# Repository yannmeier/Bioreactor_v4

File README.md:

# Bioreactor_v4

This repository is dedicated to the version 4 of the Bioreactor.

## Electronics

The architecture for v4 is articulated around one central board powered by 
an ATmega32u4 MCU relying on nilRTOS and external boards for interfacing
to extra sensors and/or LCD screeens.

The main board comes with the following features:
- stepper motor control with Neodimium magnet
- Load cell based on HX711
- PID heater control
- DS18B20+ temperature sensing
- LoRaWAN mid-range wireless communication
- 2 peristaltic pumps control
- SPI port to control a slave LCD board
- 2 I2C ports for master to slave communication to external modules
- Serial over USB
- 12V DC jack supply

There are already a few external extra modules:
- LCD SPI slave board on ATmega32u4
- pH & Conductommetry regulation I2C slave, also works as a stand alone (in development phase)
- gas flux and mix control with analogic valves, also works as a stand alone (in development phase)
- spectrophotometer immersed in the bioreactor, also works as a stand alone (in development phase)

References:
-https://www.arduino.cc/en/Main/ArduinoBoardLeonardo
-https://github.com/greiman/NilRTOS-Arduino

Revision notes:
Bioreactor V4.2:
- Changed operating frequency from 16MHz to 8MHz
- Changed operating voltage from 5V to 3.3V
- Removed 5V regulation
- Routed LoRa RST pin to MCU with additionnal pull-up
- Hack to be performed on hardware (D6<>D12) for software compatibility
Bioreactor V4.3:
- Stepper motor has individually controllable phases
- LoRa SMA PCB edge Antenna support
- Hack to be performed on hardware (D6<>D12) for software compatibility
Bioreactor V4.4:
- D6<>D12 exchanged to provide PWM PID control of the heater

## Mechanics

(Documentation coming soon)

#Bioreactor_v5

In parallel to the development of the version 4 of the Bioreactor, a version 5, relying on the 
more powerful SAMD21 (Cortex M0+ ARM) MCU and FreeRTOS is currently being studied.

References:
-https://www.arduino.cc/en/Main/ArduinoBoardZero
-http://www.freertos.org/Atmel_SAMD20_RTOS.html
-https://www.kickstarter.com/projects/rabidprototypes/neutrino-the-tiny-32-bit-arduino-zero-compatible/updates

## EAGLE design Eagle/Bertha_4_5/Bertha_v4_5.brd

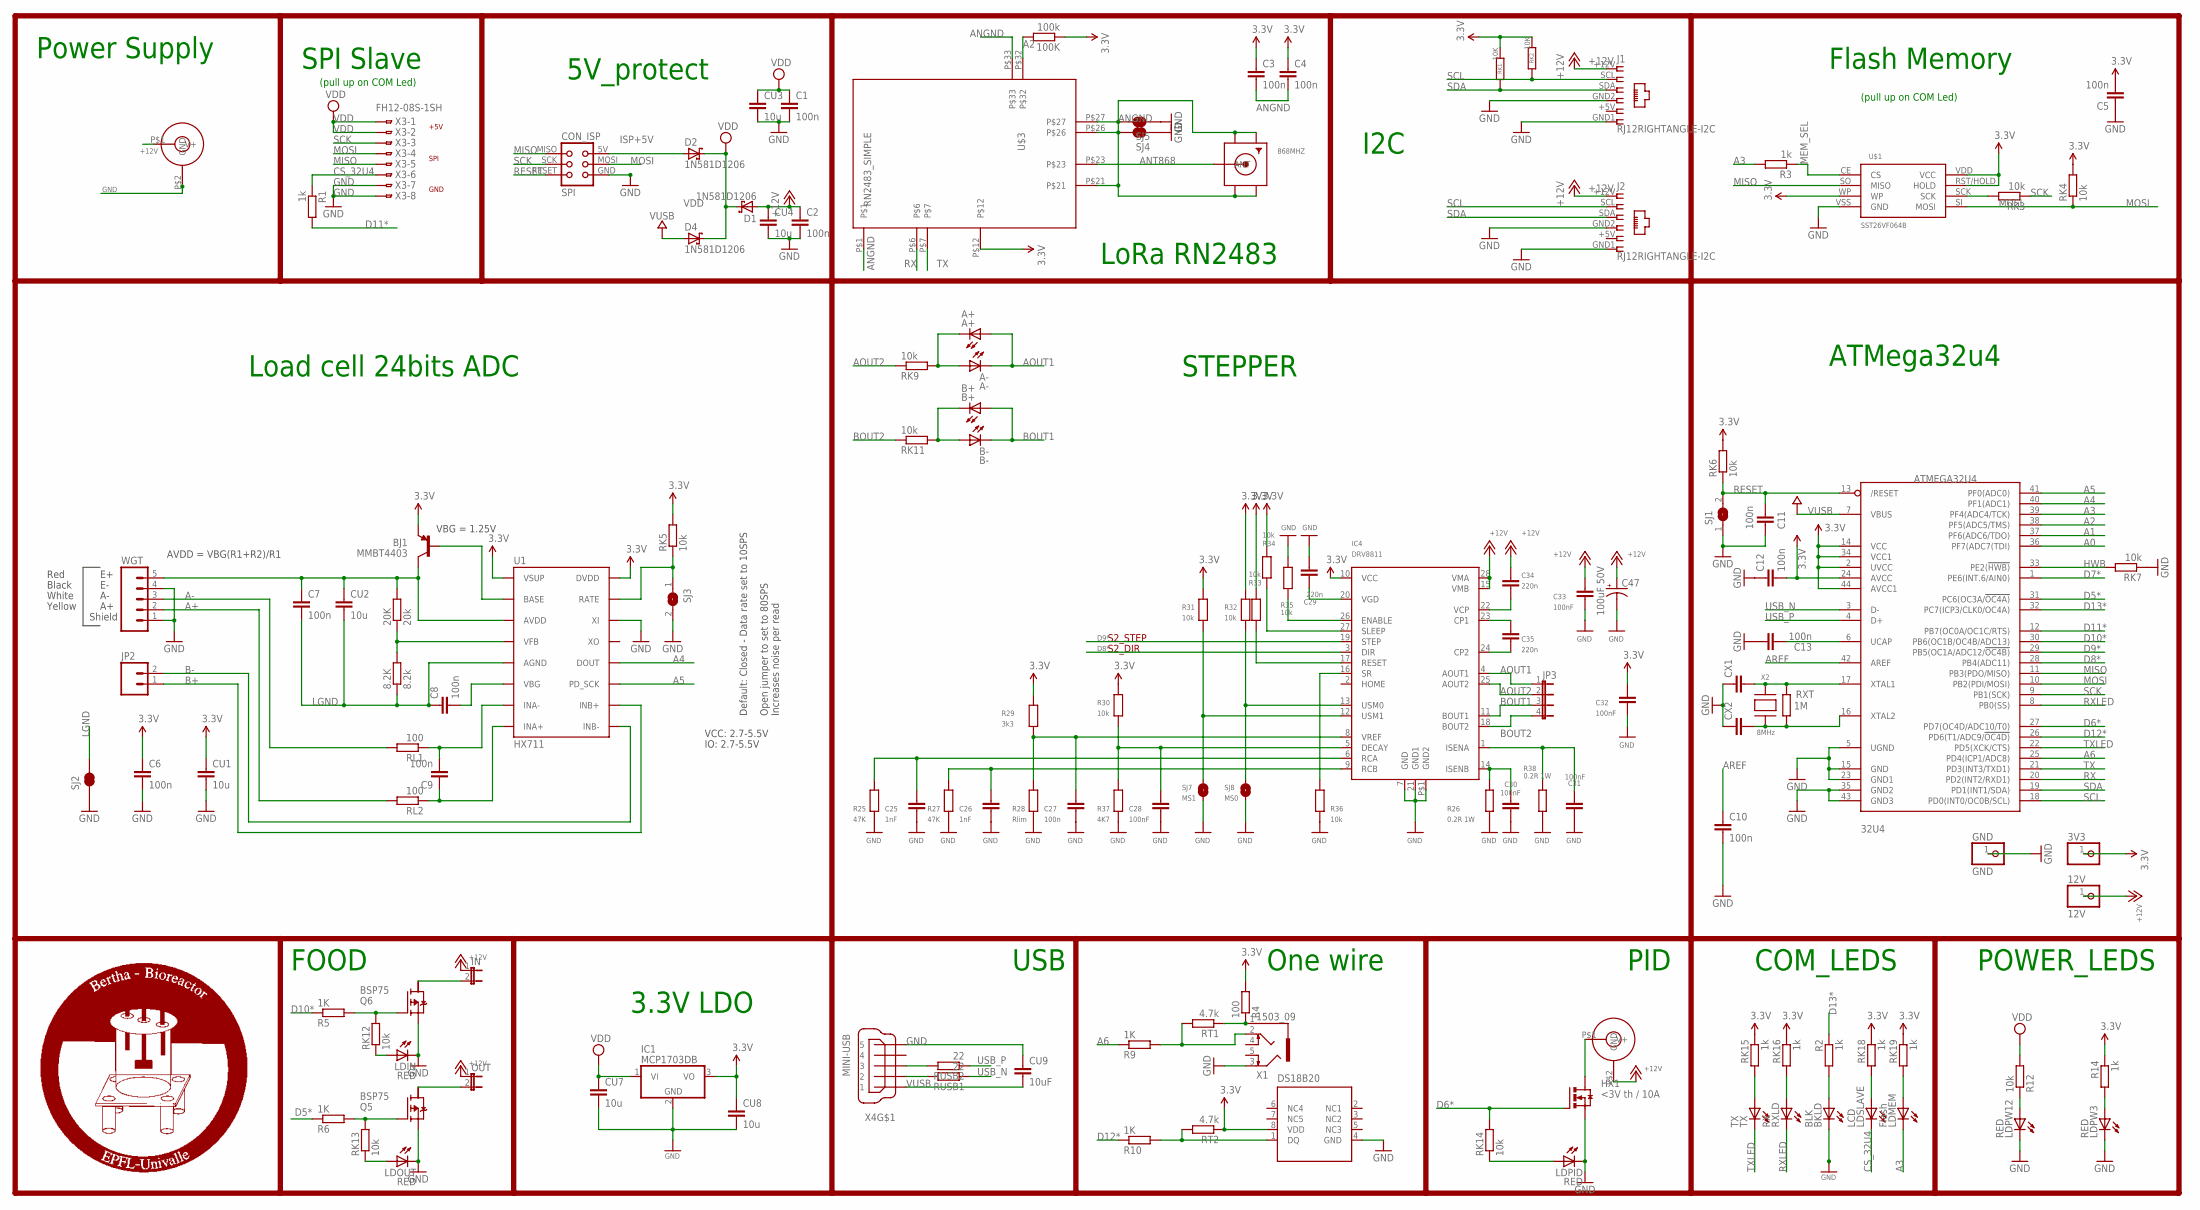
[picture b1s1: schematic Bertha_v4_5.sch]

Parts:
3V3: PINHD-1X1; 1X01
8.2K: 8.2k; M0805
12V: 12V; 1X01
20K: 20k; M0805
32U4: ATMEGA32U4; TQFP44
100K: 100k; R0805
868MHZ: SMACONNECTOR_EDGE; SMA_EDGELAUNCH
A+: A+; CHIP-LED0805
A-: A-; CHIP-LED0805
B+: B+; CHIP-LED0805
B-: B-; CHIP-LED0805
BJ1: MMBT4403; SOT23-3
BKLD: BLK; CHIP-LED0805
C1, C2, C3, C4, C5, C6, C7, C8, C9, C10, C11, C12, C13: 100n; C0805
C25, C26: 1nF; 0805
C27: 100n; 0805
C28, C30, C31, C32, C33: 100nF; 0805
C29, C34, C35: 220n; 0805
C47: 100uF 50V; PANASONIC_E
CON1, CON2: JACK_DC_BARREL; DC_BARREL
CON_ISP: SPI; TC2030-MCP-NL
CU1, CU2, CU3, CU4, CU7, CU8: 10u; C0805
CU9: 10uF; C0805
CX1, CX2: 22pF; C0805
D1, D2, D4: 1N581D1206; LED-1206
GND: GND; 1X01
HX1: <3V th / 10A; D2PACK
IC1: MCP1703DB; SOT223
IC4: DRV8811; HTSSOP28
IN: JP1E; JP1
J1, J2: RJ12RIGHTANGLE-I2C; RJ12-RIGHTANGLE-I2C
JP2: M02PTH; 1X02
JP3: JP4E; JP4
LDIN: RED; CHIP-LED0805
LDMEM: Flash; CHIP-LED0805
LDOUT: RED; CHIP-LED0805
LDPID: RED; CHIP-LED0805
LDPW3, LDPW12: RED; CHIP-LED0805
LDSLAVE: LCD; CHIP-LED0805
OUT: JP1E; JP1
Q5, Q6: BSP75; PG-SOT-223
R1, R2, R3, R14: 1k; R0805
R4: 100; R0805
R5, R6, R9, R10: 1K; R0805
R12: 10k; R0805
R25, R27: 47K; 0805
R26, R38: 0.2R 1W; R2010
R28: Rlim; 0805
R29: 3k3; 0805
R30, R31, R32, R33, R34, R35, R36: 10k; 0805
R37: 4K7; 0805
RK1, RK2: 10K; M0805
RK3, RK4, RK9, RK11, RK12, RK13, RK14: 10k; R0805
RK5, RK6, RK7: 10k; M0805
RK15, RK16, RK18, RK19: 1k; R0805
RL1, RL2: 100; M0805
RT1, RT2: 4.7k; R0805
RUSB1, RUSB2: 22; M0805
RXLD: RX; CHIP-LED0805
RXT: 1M; R0805
SJ1, SJ3: SJ
SJ2, SJ4, SJ5: JUMPER-PAD-2-NC_BY_TRACE; PAD-JUMPER-2-NC_BY_TRACE_YES_SILK
SJ7: MS1; SJ
SJ8: MS0; SJ
TX: TX; CHIP-LED0805
U1: HX711; SO16
U$1: SST26VF064B; SOIC_8-LEAD
U$2: DS18B20; MSOP8
U$3: RN2483_SIMPLE
WGT: M05PTH; 1X05
X1: 1503_09
X2: 8MHz; NX6035
X3: FH12-08S-1SH
X4: MINI-USB; 32005-201

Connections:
3.3V: 3V3.1, 32U4.2 (UVCC), 32U4.14 (VCC), 32U4.24 (AVCC), 32U4.34 (VCC1), 32U4.44 (AVCC1), 100K.1, BJ1.2 (E), C3.1, C4.1, C5.2, C6.1, C12.2, C32.1, CU1.1, CU8.1, IC1.3 (VO), IC4.10 (VCC), R4.2, R14.1, R29.2, R30.2, R31.2, R32.2, R33.2, R34.2, RK1.1, RK2.1, RK4.2, RK5.2, RK6.2, RK15.1, RK16.1, RK18.1, RK19.1, RT2.1, U1.1 (VSUP), U1.16 (DVDD), U$1.RST/HOLD (HOLD), U$1.VDD (VCC), U$1.WP, U$2.8 (VDD), U$3.P$12
5: J1.+5V (5), J2.+5V (5)
+12V: 12V.1, C2.1, C33.1, C34.1, C47.+, CON1.P$1 (V+), CON2.P$2 (GND), CU4.1, D1.A, IC4.15 (VMB), IC4.28 (VMA), IN.1, J1.+12V (1), J2.+12V (1), OUT.1
A0: 32U4.36 (PF7(ADC7(TDI))
A1: 32U4.37 (PF6(ADC6/TDO))
A2: 32U4.38 (PF5(ADC5/TMS)), 100K.2, U$3.P$32
A3: 32U4.39 (PF4(ADC4/TCK)), LDMEM.C, R3.2
A4: 32U4.40 (PF1(ADC1)), U1.12 (DOUT)
A5: 32U4.41 (PF0(ADC0)), U1.11 (PD_SCK)
A6: 32U4.25 (PD4(ICP1/ADC8)), R9.1
A+: RL2.2, WGT.2
A-: RL1.2, WGT.3
ANGND: 868MHZ.GND@1 (GND4), 868MHZ.GND@2 (GND3), 868MHZ.GND@3 (GND2), 868MHZ.GND@4 (GND1), C3.2, C4.2, SJ4.2, SJ5.2, U$3.P$1, U$3.P$21, U$3.P$26, U$3.P$27, U$3.P$33
ANT868: 868MHZ.P (ANT), U$3.P$23
AOUT1: A+.A, A-.C, IC4.4 (AOUT1), JP3.1
AOUT2: IC4.25 (AOUT2), JP3.2, RK9.1
AREF: 32U4.42 (AREF), C10.1
B+: JP2.1, U1.10 (INB+)
B-: JP2.2, U1.9 (INB-)
BOUT1: B+.A, B-.C, IC4.11 (BOUT1), JP3.3
BOUT2: IC4.18 (BOUT2), JP3.4, RK11.1
CN3: C8.2, U1.6 (VBG)
CS_32U4: LDSLAVE.C, R1.1, X3.6
D5*: 32U4.31 (PC6(OC3A/!OC4A)), R6.1
D6*: 32U4.27 (PD7(OC4D/ADC10/T0)), HX1.1 (G), RK14.2
D7*: 32U4.1 (PE6(INT.6/AIN0))
D8*: 32U4.28 (PB4(ADC11)), IC4.3 (DIR)
D9*: 32U4.29 (PB5(OC1A/ADC12/!OC4B)), IC4.19 (STEP)
D10*: 32U4.30 (PB6(OC1B/OC4B/ADC13)), R5.1
D11*: 32U4.12 (PB7(OC0A/OC1C/RTS)), R1.2
D12*: 32U4.26 (PD6(T1/ADC9/!OC4D)), R10.1
D13*: 32U4.32 (PC7(ICP3/CLK0/OC4A)), R2.1
GND: 32U4.5 (UGND), 32U4.15 (GND), 32U4.23 (GND1), 32U4.35 (GND2), 32U4.43 (GND3), BKLD.C, C1.2, C2.2, C5.1, C6.2, C10.2, C11.2, C12.1, C13.1, C25.2, C26.2, C27.2, C28.2, C29.2, C30.2, C31.2, C32.2, C33.2, C47.-, CON1.P$2 (GND), CON_ISP.GND, CU1.2, CU3.2, CU4.2, CU7.2, CU8.2, CU9.1, CX1.1, CX2.1, GND.1, HX1.3 (S), IC1.2 (GND), IC4.7 (GND), IC4.21 (GND1), IC4.P$1 (GND2), J1.GND1 (6), J1.GND2 (4), J2.GND1 (6), J2.GND2 (4), LDIN.C, LDOUT.C, LDPID.C, LDPW3.C, LDPW12.C, Q5.3 (S), Q6.3 (S), R25.1, R26.1, R27.1, R28.1, R35.1, R36.1, R37.1, R38.1, RK7.1, SJ1.1, SJ2.1, SJ3.2, SJ4.1, SJ5.1, SJ7.1, SJ8.1, U1.14 (XI), U$1.VSS (GND), U$2.4 (GND), WGT.1, WGT.4, X1.3, X3.7, X3.8, X4.5
HWB: 32U4.33 (PE2(!HWB)), RK7.2
ISP+5V: CON_ISP.5V (VCC), D2.A
LGND: 8.2K.1, C7.2, C8.1, CU2.2, SJ2.2, U1.5 (AGND)
MEM_SEL: R3.1, U$1.CE (CS)
MISO: 32U4.11 (PB3(PDO/MISO)), CON_ISP.MISO, U$1.SO (MISO), X3.5
MOSI: 32U4.10 (PB2(PDI/MOSI)), CON_ISP.MOSI, RK4.1, U$1.SI (MOSI), X3.4
unnamed: 32U4.6 (UCAP), C13.2
unnamed: CON2.P$1 (V+), HX1.2 (D)
unnamed: BKLD.A, R2.2
unnamed: 20K.2, BJ1.3 (C), C7.1, CU2.1, U1.3 (AVDD), WGT.5
unnamed: LDPW12.A, R12.1
unnamed: Q6.1 (G), R5.2, RK12.2
unnamed: R10.2, RT2.2, U$2.1 (DQ)
unnamed: Q5.1 (G), R6.2, RK13.2
unnamed: C35.2, IC4.24 (CP2)
unnamed: OUT.2, Q5.2 (D)
unnamed: R4.1, RT1.1, X1.1
unnamed: A+.C, A-.A, RK9.2
unnamed: IN.2, Q6.2 (D)
unnamed: RK15.2, TX.A
unnamed: B+.C, B-.A, RK11.2
unnamed: C9.2, RL1.1, U1.7 (INA-)
unnamed: R9.2, RT1.2, X1.2
unnamed: LDSLAVE.A, RK18.2
unnamed: RK3.2, U$1.SCK
unnamed: RK16.2, RXLD.A
unnamed: LDMEM.A, RK19.2
unnamed: LDPID.A, RK14.1
unnamed: LDIN.A, RK12.1
unnamed: LDOUT.A, RK13.1
unnamed: C35.1, IC4.23 (CP1)
unnamed: C34.2, IC4.22 (VCP)
unnamed: LDPW3.A, R14.2
unnamed: C29.1, IC4.20 (VGD)
unnamed: C31.1, IC4.1 (ISENA), R38.2
unnamed: BJ1.1 (B), U1.2 (BASE)
unnamed: 8.2K.2, 20K.1, U1.4 (VFB)
unnamed: C30.1, IC4.14 (ISENB), R26.2
unnamed: RK5.1, SJ3.1, U1.15 (RATE)
unnamed: 32U4.17 (XTAL1), CX1.2, RXT.2, X2.P$2
unnamed: C9.1, RL2.1, U1.8 (INA+)
unnamed: C28.1, IC4.5 (DECAY), R30.1, R37.2
unnamed: C25.1, IC4.6 (RCA), R25.2
unnamed: C26.1, IC4.9 (RCB), R27.2
unnamed: IC4.27 (SLEEP), R34.1
unnamed: IC4.17 (RESET), R33.1
unnamed: C27.1, IC4.8 (VREF), R28.2, R29.1
unnamed: IC4.26 (ENABLE), R35.2
unnamed: IC4.12 (USM1), R31.1, SJ7.2
unnamed: IC4.13 (USM0), R32.1, SJ8.2
unnamed: IC4.16 (SR), R36.2
RESET: 32U4.13 (/RESET), C11.1, CON_ISP.RESET, RK6.1, SJ1.2
RX: 32U4.20 (PD2(INT2/RXD1)), U$3.P$6
RXLED: 32U4.8 (PB0(SS)), RXLD.C
SCK: 32U4.9 (PB1(SCK)), CON_ISP.SCK, RK3.1, X3.3
SCL: 32U4.18 (PD0(INT0/OC0B/SCL)), J1.SCL (2), J2.SCL (2), RK2.2
SDA: 32U4.19 (PD1(INT1/SDA)), J1.SDA (3), J2.SDA (3), RK1.2
TX: 32U4.21 (PD3(INT3/TXD1)), U$3.P$7
TXLED: 32U4.22 (PD5(XCK/CTS)), TX.C
USBC_N: RUSB1.2, X4.2
USBC_P: RUSB2.2, X4.3
USB_N: 32U4.3 (D-), RUSB1.1
USB_P: 32U4.4 (D+), RUSB2.1
VDD: C1.1, CU3.1, CU7.1, D1.C, D2.C, D4.C, IC1.1 (VI), R12.2, X3.1, X3.2
VUSB: 32U4.7 (VBUS), CU9.2, D4.A, X4.1
XTAL1: 32U4.16 (XTAL2), CX2.2, RXT.1, X2.P$1

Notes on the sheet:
Flash Memory
USB
Power Supply
LoRa RN2483
PID
One wire
I2C
5V_protect
POWER_LEDS
COM_LEDS
3.3V LDO
STEPPER
VCC: 2.7-5.5V
VBG = 1.25V
AVDD = VBG(R1+R2)/R1
Default: Closed - Data rate set to 10SPS
Open jumper to set to 80SPS Increases noise per read
Red
Black
White
IO: 2.7-5.5V
Shield
Yellow
ATMega32u4
Load cell 24bits ADC
SPI Slave
GND
+5V
SPI
FOOD
(pull up on COM Led)
S2_DIR
S2_STEP

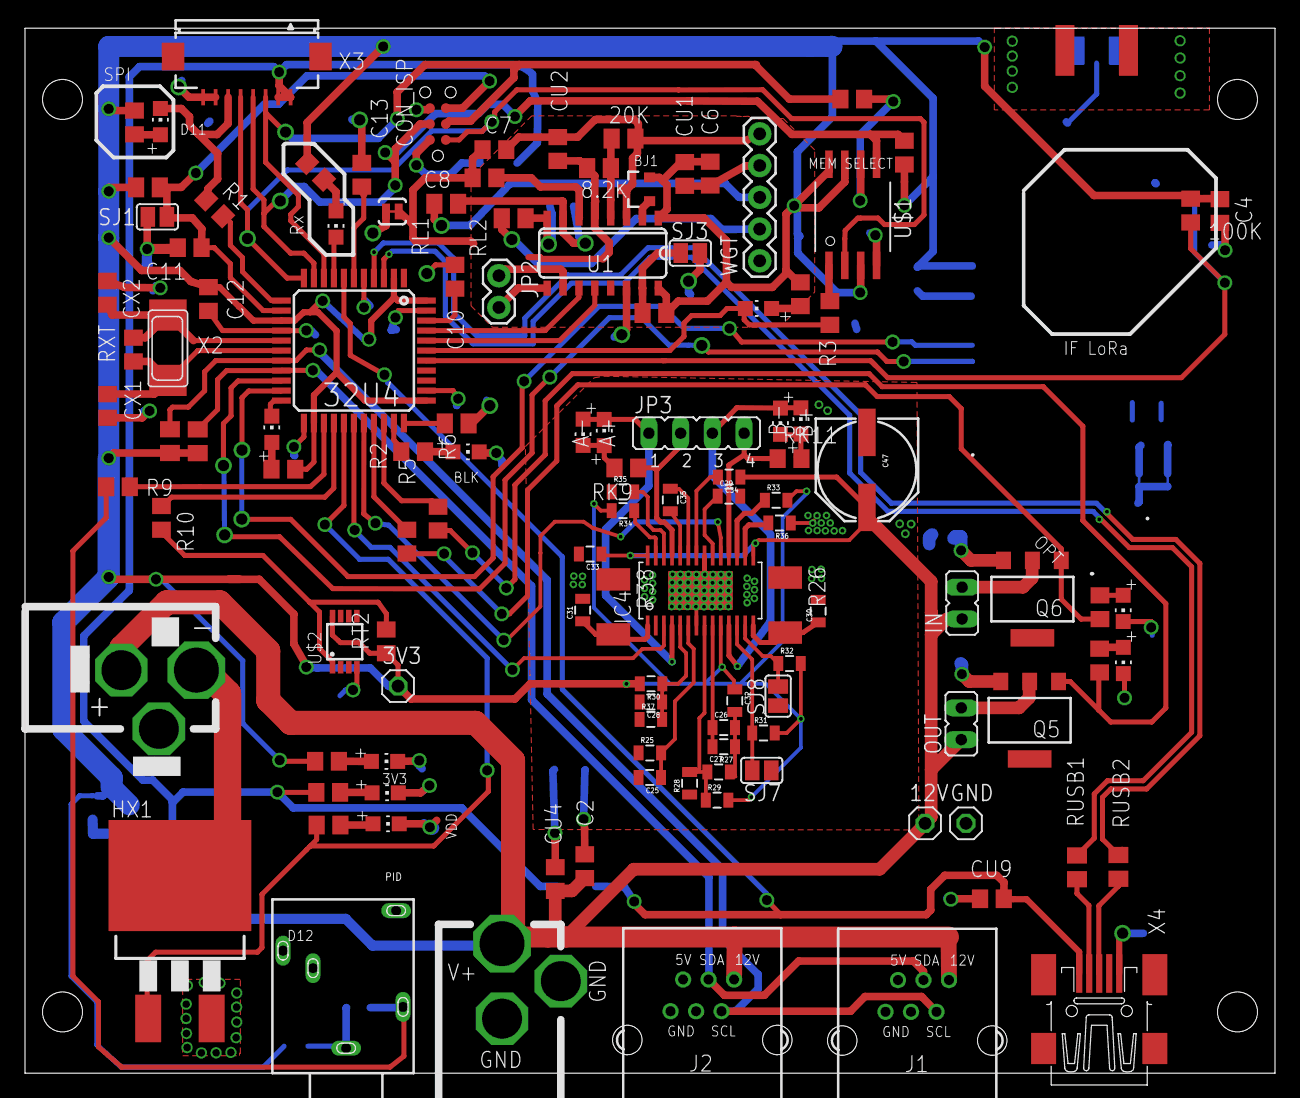
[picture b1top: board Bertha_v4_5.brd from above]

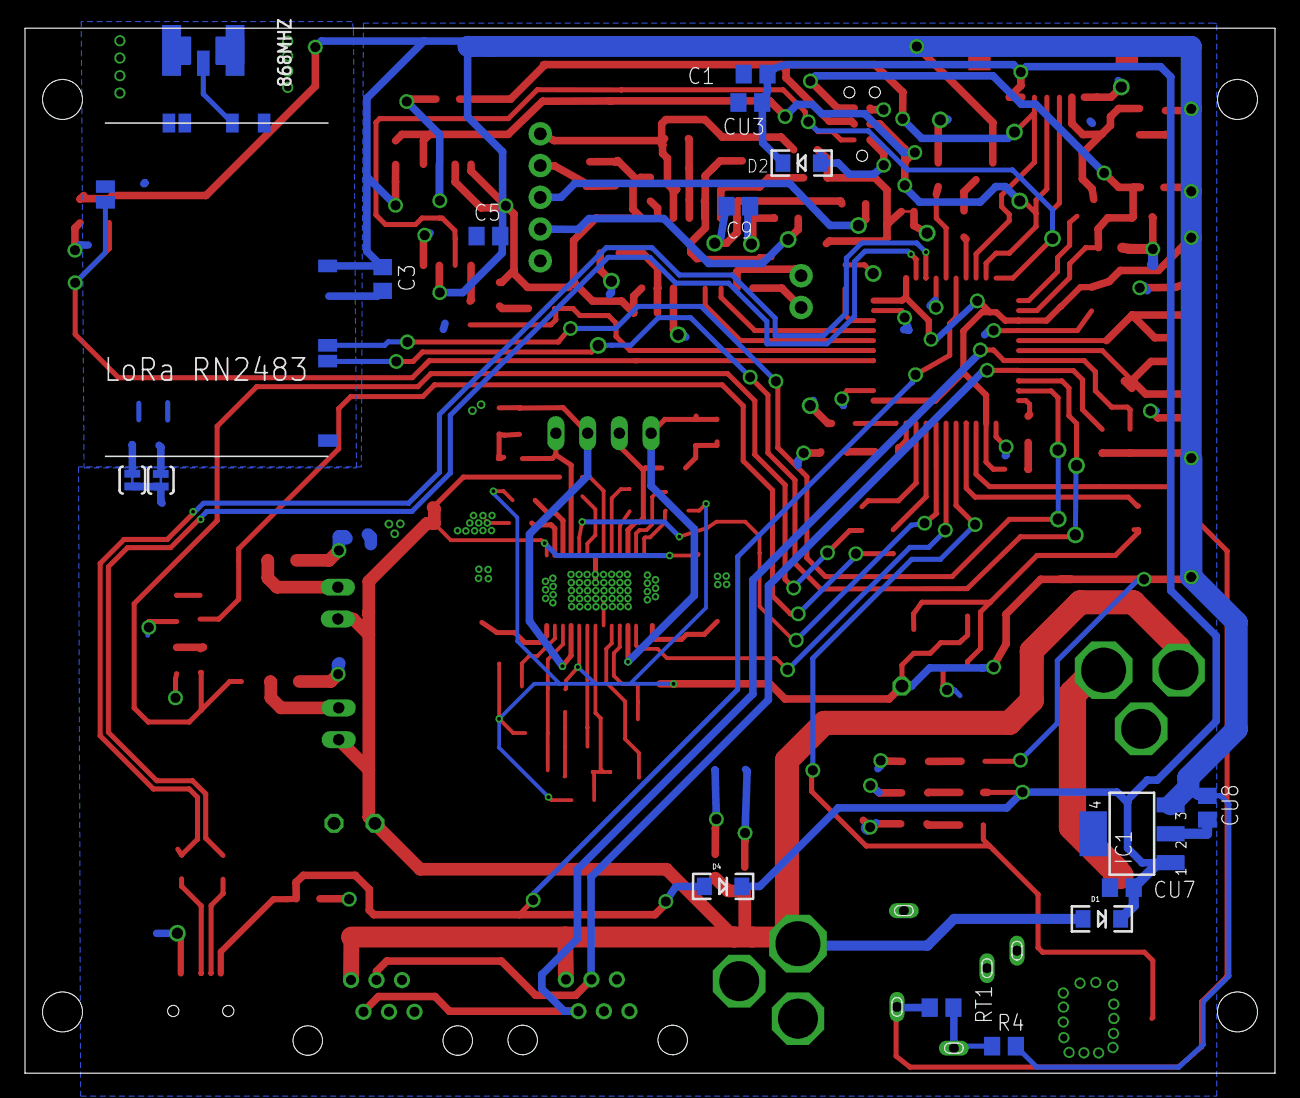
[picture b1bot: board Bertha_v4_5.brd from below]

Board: 4 copper layers, 100.0 x 83.6 mm, 137 parts (17 on the bottom side), 96 nets.

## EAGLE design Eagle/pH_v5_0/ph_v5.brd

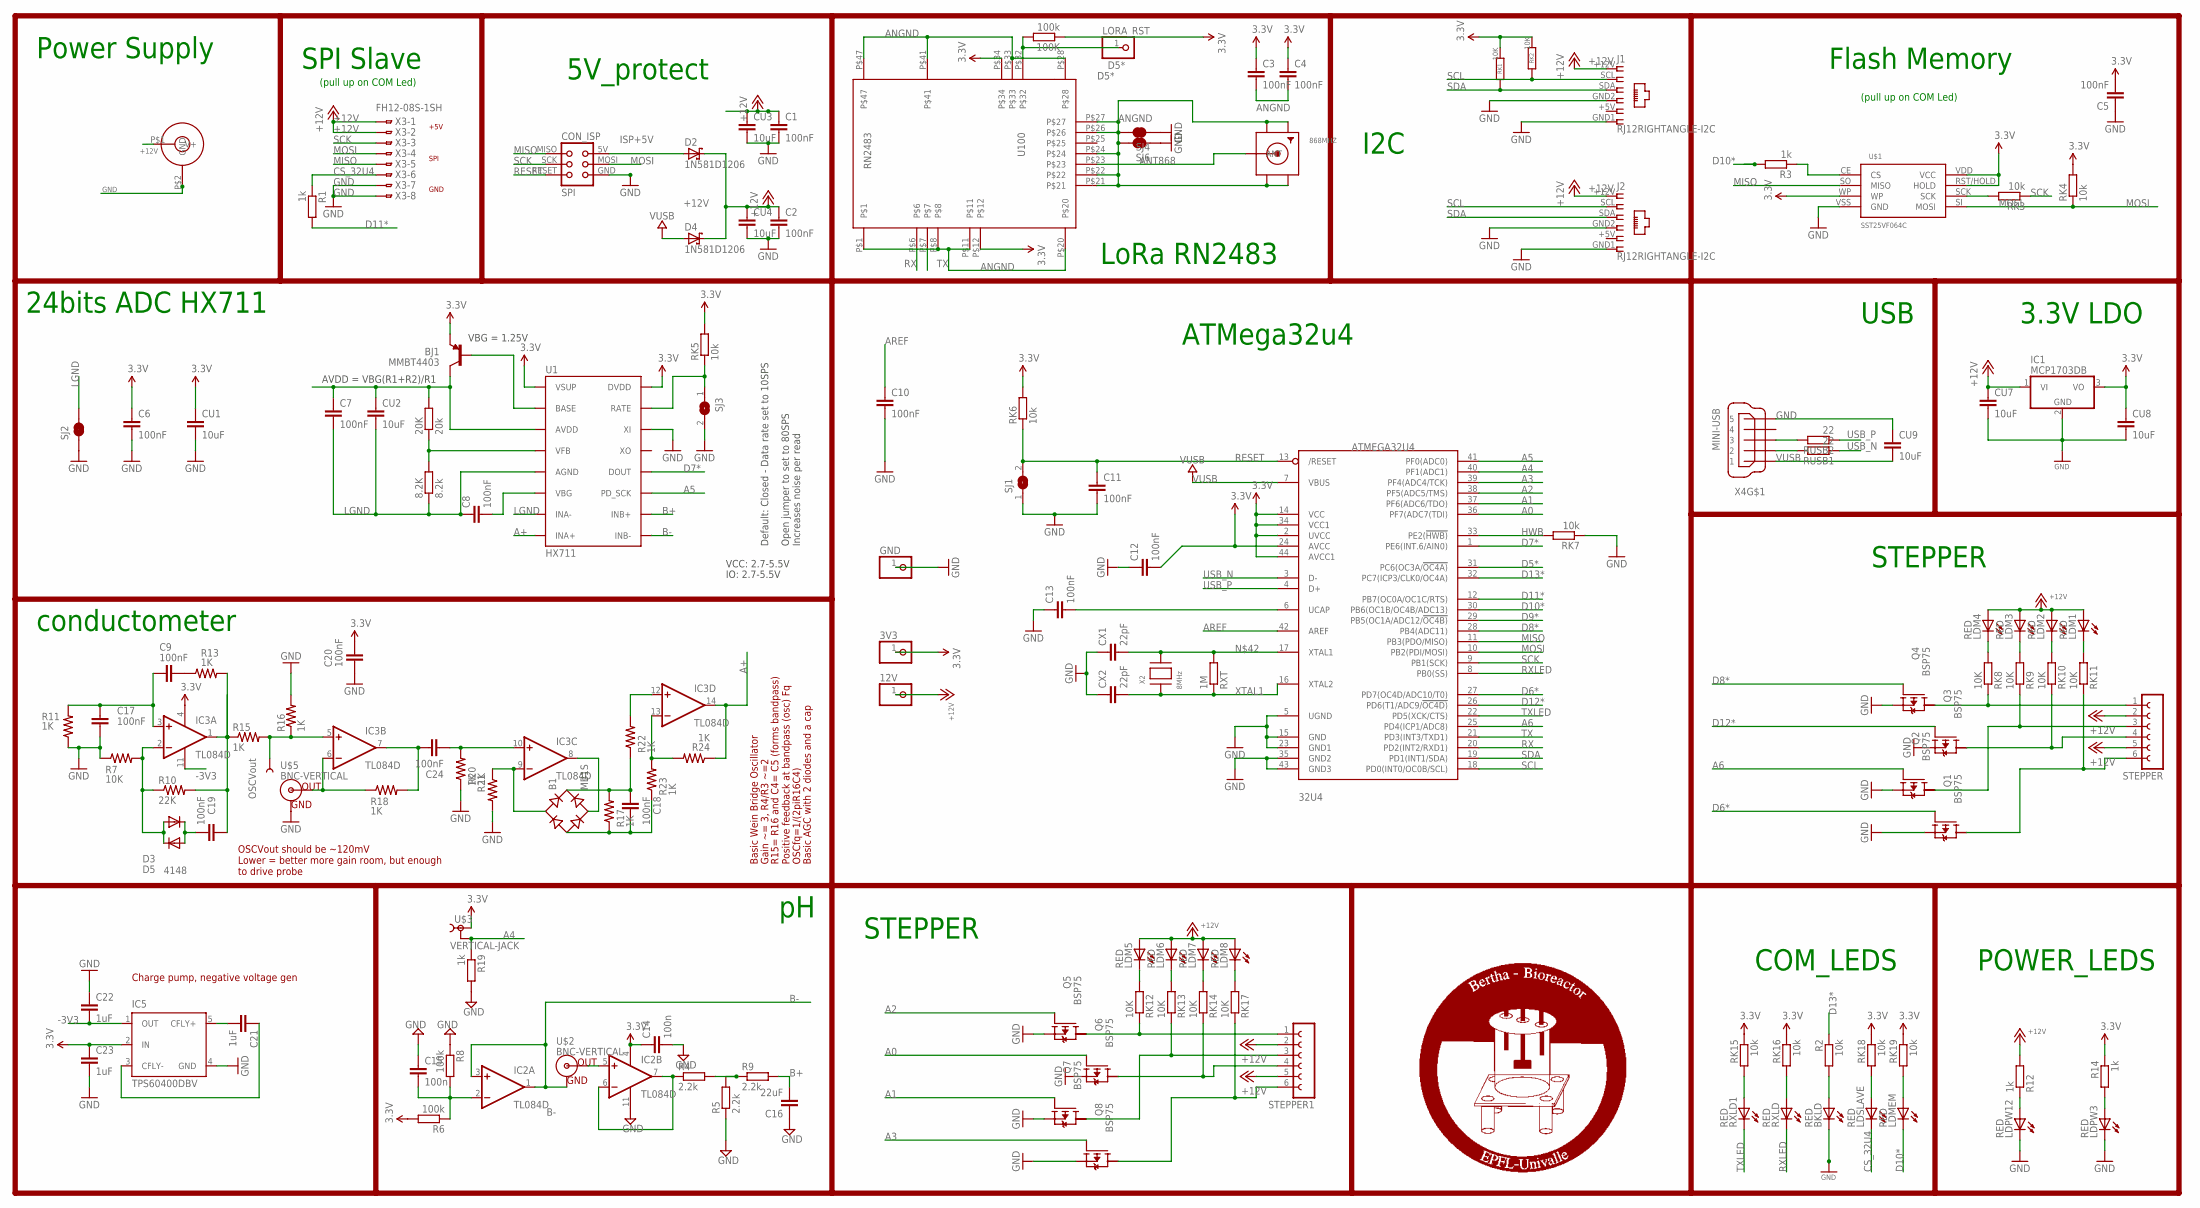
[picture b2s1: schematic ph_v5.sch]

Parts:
3V3, 12V: PINHD-1X1; 1X01
8.2K: 8.2k; M0805
20K: 20k; M0805
32U4: ATMEGA32U4; TQFP44
100K: 100k; R0805
868MHZ: SMACONNECTOR_EDGE; SMA_EDGELAUNCH
B1: MB1S; SOIC-4
BJ1: MMBT4403; SOT23-3
BKLD: RED; CHIP-LED0805
C1, C2, C3, C4, C5, C6, C7, C8, C10, C11, C12, C13: 100nF; C1206
C9, C17, C18, C19, C20, C24: 100nF; 1206
C14, C15: 100n; C1206
C16: 22uF; C1206
C21, C22, C23: 1uF; 1206
CON1: JACK_DC_BARREL; DC_BARREL
CON_ISP: SPI; TC2030-MCP-NL
CU1, CU2, CU3, CU4, CU7, CU8, CU9: 10uF; C1206
CX1, CX2: 22pF; C1206
D2, D4: 1N581D1206; LED-1206
D3, D5: 4148; SOD123
GND: PINHD-1X1; 1X01
IC1: MCP1703DB; SOT223
IC2, IC3: TL084D; SO14
IC5: TPS60400DBV; SOT23-DBV
J1, J2: RJ12RIGHTANGLE-I2C; RJ12-RIGHTANGLE-I2C
LDM1, LDM2, LDM3, LDM4, LDM5, LDM6, LDM7, LDM8: RED; CHIP-LED0805
LDMEM: RED; CHIP-LED0805
LDPW3, LDPW12: RED; CHIP-LED0805
LDSLAVE: RED; CHIP-LED0805
LORA_RST: PINHD-1X1; 1X01
Q1, Q2, Q3, Q4, Q5, Q6, Q7, Q8: BSP75; PG-SOT-223
R1, R3, R12, R14, R19: 1k; R0805
R2: 10k; R0805
R4, R5, R9: 2.2k; R0805
R6, R8: 100k; R0805
R7: 10K; 0805
R10: 22K; 0805
R11, R13, R15, R16, R17, R18, R20, R21, R22, R23, R24: 1K; 0805
RK1, RK2: 10K; M0805
RK3, RK4, RK15, RK16, RK18, RK19: 10k; R0805
RK5, RK6, RK7: 10k; M0805
RK8, RK9, RK10, RK11, RK12, RK13, RK14, RK17: 10K; R0805
RUSB1, RUSB2: 22; M1206
RXLD, RXLD1: RED; CHIP-LED0805
RXT: 1M; R0805
SJ1, SJ3: SJ
SJ2, SJ4, SJ6: JUMPER-PAD-2-NC_BY_TRACE; PAD-JUMPER-2-NC_BY_TRACE_YES_SILK
STEPPER, STEPPER1: FE06-1; FE06
TP5: OSCVout; PAD.03X.03
U1: HX711; SO16
U100: RN2483
U$1: SST25VF064C; SOIC_8-LEAD
U$2, U$5: BNC-VERTICAL
U$3: VERTICAL-JACK
X2: 8MHz; NX6035
X3: FH12-08S-1SH
X4: MINI-USB; 32005-201

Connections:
3.3V: 3V3.1, 32U4.2 (UVCC), 32U4.14 (VCC), 32U4.24 (AVCC), 32U4.34 (VCC1), 32U4.44 (AVCC1), 100K.1, BJ1.2 (E), C3.1, C4.1, C5.2, C6.1, C12.2, C14.1, C20.1, C23.1, CU1.1, CU8.1, IC1.3 (VO), IC2.4 (V+), IC3.4 (V+), IC5.2 (IN), R6.2, R14.1, RK1.1, RK2.1, RK4.2, RK5.2, RK6.2, RK15.1, RK16.1, RK18.1, RK19.1, U1.1 (VSUP), U1.16 (DVDD), U100.P$12, U100.P$34, U$1.RST/HOLD (HOLD), U$1.VDD (VCC), U$1.WP, U$3.P$1 (1)
+12V: 12V.1, C1.1, C2.1, CON1.P$1 (V+), CU3.1, CU4.1, CU7.1, D2.C, D4.C, IC1.1 (VI), J1.+12V (1), J2.+12V (1), LDM1.A, LDM2.A, LDM3.A, LDM4.A, LDM5.A, LDM6.A, LDM7.A, LDM8.A, R12.2, STEPPER.2, STEPPER.5, STEPPER1.2, STEPPER1.5, X3.1, X3.2
-3V3: C22.2, IC3.11 (V-), IC5.1 (OUT)
A0: 32U4.36 (PF7(ADC7(TDI)), Q6.1 (G)
A1: 32U4.37 (PF6(ADC6/TDO)), Q7.1 (G)
A2: 32U4.38 (PF5(ADC5/TMS)), Q5.1 (G)
A3: 32U4.39 (PF4(ADC4/TCK)), Q8.1 (G)
A4: 32U4.40 (PF1(ADC1)), R19.1, U$3.P$2 (2)
A5: 32U4.41 (PF0(ADC0)), U1.11 (PD_SCK)
A6: 32U4.25 (PD4(ICP1/ADC8)), Q2.1 (G)
A+: IC3.14 (OUT), R24.1, U1.8 (INA+)
ANGND: 868MHZ.GND@1 (GND4), 868MHZ.GND@2 (GND3), 868MHZ.GND@3 (GND2), 868MHZ.GND@4 (GND1), C3.2, C4.2, SJ4.2, SJ6.2, U100.P$1, U100.P$8, U100.P$11, U100.P$20, U100.P$21, U100.P$22, U100.P$24, U100.P$26, U100.P$27, U100.P$28, U100.P$33, U100.P$41, U100.P$47
ANT868: 868MHZ.P (ANT), U100.P$23
AREF: 32U4.42 (AREF), C10.1
B+: C16.2, R9.2, U1.10 (INB+)
B-: IC2.1 (OUT), IC2.3 (+IN), U1.9 (INB-), U$2.G (GND)
CN3: C8.2, U1.6 (VBG)
CS_32U4: LDSLAVE.C, R1.1, X3.6
D5*: 32U4.31 (PC6(OC3A/!OC4A)), 100K.2, LORA_RST.1, U100.P$32
D6*: 32U4.27 (PD7(OC4D/ADC10/T0)), Q1.1 (G)
D7*: 32U4.1 (PE6(INT.6/AIN0)), U1.12 (DOUT)
D8*: 32U4.28 (PB4(ADC11)), Q4.1 (G)
D9*: 32U4.29 (PB5(OC1A/ADC12/!OC4B))
D10*: 32U4.30 (PB6(OC1B/OC4B/ADC13)), LDMEM.C, R3.2
D11*: 32U4.12 (PB7(OC0A/OC1C/RTS)), R1.2
D12*: 32U4.26 (PD6(T1/ADC9/!OC4D)), Q3.1 (G)
D13*: 32U4.32 (PC7(ICP3/CLK0/OC4A)), R2.1
GND: 32U4.5 (UGND), 32U4.15 (GND), 32U4.23 (GND1), 32U4.35 (GND2), 32U4.43 (GND3), BKLD.C, C1.2, C2.2, C5.1, C6.2, C10.2, C11.2, C12.1, C13.1, C14.2, C15.1, C16.1, C17.1, C20.2, C22.1, C23.2, CON1.P$2 (GND), CON_ISP.GND, CU1.2, CU3.2, CU4.2, CU7.2, CU8.2, CU9.1, CX1.1, CX2.1, GND.1, IC1.2 (GND), IC2.11 (V-), IC5.4 (GND), J1.GND1 (6), J1.GND2 (4), J2.GND1 (6), J2.GND2 (4), LDPW3.C, LDPW12.C, Q1.3 (S), Q2.3 (S), Q3.3 (S), Q4.3 (S), Q5.3 (S), Q6.3 (S), Q7.3 (S), Q8.3 (S), R5.1, R7.1, R8.1, R11.1, R16.2, R19.2, R20.1, R21.2, RK7.1, SJ1.1, SJ2.1, SJ3.2, SJ4.1, SJ6.1, U1.14 (XI), U$1.VSS (GND), U$5.G (GND), X3.7, X3.8, X4.5
HWB: 32U4.33 (PE2(!HWB)), RK7.2
ISP+5V: CON_ISP.5V (VCC), D2.A
LGND: 8.2K.1, C7.2, C8.1, CU2.2, SJ2.2, U1.5 (AGND), U1.7 (INA-)
MISO: 32U4.11 (PB3(PDO/MISO)), CON_ISP.MISO, U$1.SO (MISO), X3.5
MOSI: 32U4.10 (PB2(PDI/MOSI)), CON_ISP.MOSI, RK4.1, U$1.SI (MOSI), X3.4
unnamed: 32U4.6 (UCAP), C13.2
unnamed: Q5.2 (D), RK12.1, STEPPER1.1
unnamed: BKLD.A, R2.2
unnamed: Q7.2 (D), RK13.1, STEPPER1.3
unnamed: 20K.2, BJ1.3 (C), C7.1, CU2.1, U1.3 (AVDD)
unnamed: Q6.2 (D), RK14.1, STEPPER1.4
unnamed: LDPW12.A, R12.1
unnamed: Q8.2 (D), RK17.1, STEPPER1.6
unnamed: LDM5.C, RK12.2
unnamed: R3.1, U$1.CE (CS)
unnamed: LDM6.C, RK13.2
unnamed: LDM7.C, RK14.2
unnamed: LDM8.C, RK17.2
unnamed: Q4.2 (D), RK8.1, STEPPER.1
unnamed: Q2.2 (D), RK9.1, STEPPER.3
unnamed: Q3.2 (D), RK10.1, STEPPER.4
unnamed: R4.2, R5.2, R9.1
unnamed: D3.A, D5.C, IC3.2 (-IN), R7.2, R10.1
unnamed: Q1.2 (D), RK11.1, STEPPER.6
unnamed: C9.1, R13.1
unnamed: IC2.5 (+IN), U$2.S (OUT)
unnamed: LDSLAVE.A, RK18.2
unnamed: RK3.2, U$1.SCK
unnamed: RK16.2, RXLD.A
unnamed: LDMEM.A, RK19.2
unnamed: C19.1, IC3.1 (OUT), R10.2, R13.2, R15.1
unnamed: C15.2, IC2.2 (-IN), R6.1, R8.2
unnamed: IC2.6 (-IN), IC2.7 (OUT), R4.1
unnamed: IC3.5 (+IN), R15.2, R16.1, TP5.P$1
unnamed: C9.2, C17.2, IC3.3 (+IN), R11.2
unnamed: LDM4.C, RK8.2
unnamed: LDM3.C, RK9.2
unnamed: LDM2.C, RK10.2
unnamed: LDPW3.A, R14.2
unnamed: IC3.6 (-IN), R18.1, U$5.S (OUT)
unnamed: C24.1, IC3.7 (OUT), R18.2
unnamed: LDM1.C, RK11.2
unnamed: BJ1.1 (B), U1.2 (BASE)
unnamed: 8.2K.2, 20K.1, U1.4 (VFB)
unnamed: C24.2, IC3.10 (+IN), R20.2
unnamed: RK5.1, SJ3.1, U1.15 (RATE)
unnamed: 32U4.17 (XTAL1), CX1.2, RXT.2, X2.P$2
unnamed: B1.~2 (AC2), IC3.8 (OUT)
unnamed: C19.2, D3.C, D5.A
unnamed: C21.1, IC5.3 (CFLY-)
unnamed: C21.2, IC5.5 (CFLY+)
unnamed: B1.-, C18.1, R17.1, R23.1
unnamed: B1.~1 (AC1), IC3.9 (-IN), R21.1
unnamed: B1.+, C18.2, R17.2, R22.1
unnamed: IC3.12 (+IN), R22.2
unnamed: IC3.13 (-IN), R23.2, R24.2
unnamed: RK15.2, RXLD1.A
RESET: 32U4.13 (/RESET), C11.1, CON_ISP.RESET, RK6.1, SJ1.2
RX: 32U4.20 (PD2(INT2/RXD1)), U100.P$6
RXLED: 32U4.8 (PB0(SS)), RXLD.C
SCK: 32U4.9 (PB1(SCK)), CON_ISP.SCK, RK3.1, X3.3
SCL: 32U4.18 (PD0(INT0/OC0B/SCL)), J1.SCL (2), J2.SCL (2), RK2.2
SDA: 32U4.19 (PD1(INT1/SDA)), J1.SDA (3), J2.SDA (3), RK1.2
TX: 32U4.21 (PD3(INT3/TXD1)), U100.P$7
TXLED: 32U4.22 (PD5(XCK/CTS)), RXLD1.C
USBC_N: RUSB1.2, X4.2
USBC_P: RUSB2.2, X4.3
USB_N: 32U4.3 (D-), RUSB1.1
USB_P: 32U4.4 (D+), RUSB2.1
VUSB: 32U4.7 (VBUS), CU9.2, D4.A, X4.1
XTAL1: 32U4.16 (XTAL2), CX2.2, RXT.1, X2.P$1

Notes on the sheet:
Flash Memory
USB
Power Supply
LoRa RN2483
I2C
5V_protect
POWER_LEDS
COM_LEDS
3.3V LDO
STEPPER
VCC: 2.7-5.5V
VBG = 1.25V
AVDD = VBG(R1+R2)/R1
Default: Closed - Data rate set to 10SPS
Open jumper to set to 80SPS Increases noise per read
IO: 2.7-5.5V
ATMega32u4
24bits ADC HX711
SPI Slave
GND
+5V
SPI
(pull up on COM Led)
Basic Wein Bridge Oscillator
Gain ~= 3, R4/R3 ~=2
R15= R16 and C4= C5 (forms bandpass) Positive feedback at bandpass (osc) Fq
OSCfq=1/(2piR16C4)
Basic AGC with 2 diodes and a cap
OSCVout should be ~120mV Lower = better more gain room, but enough to drive probe
conductometer
Charge pump, negative voltage gen

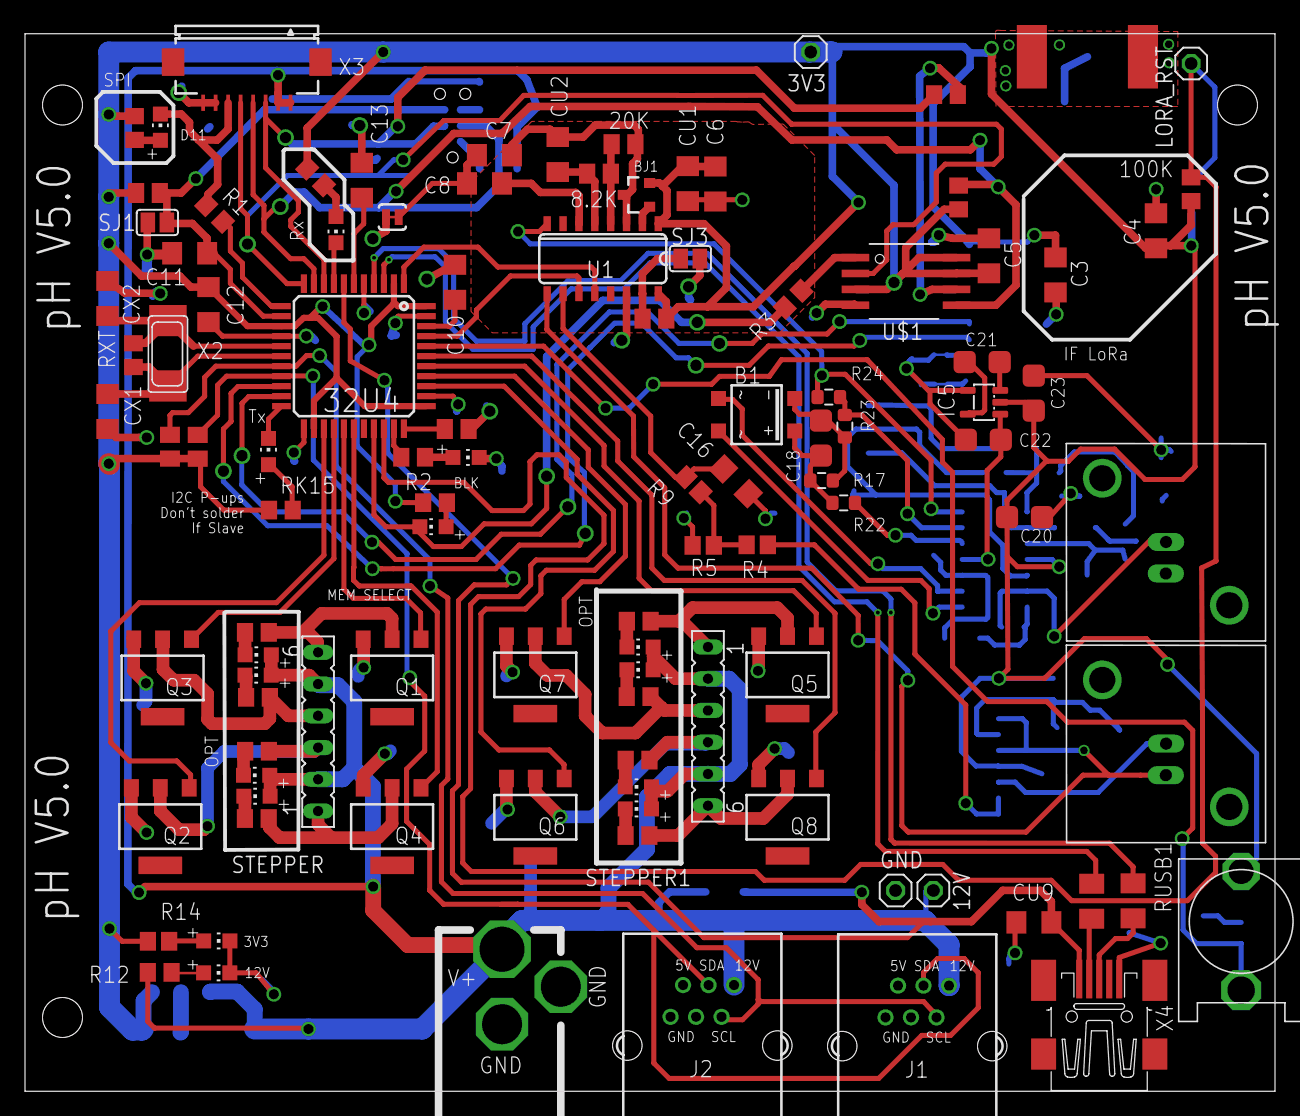
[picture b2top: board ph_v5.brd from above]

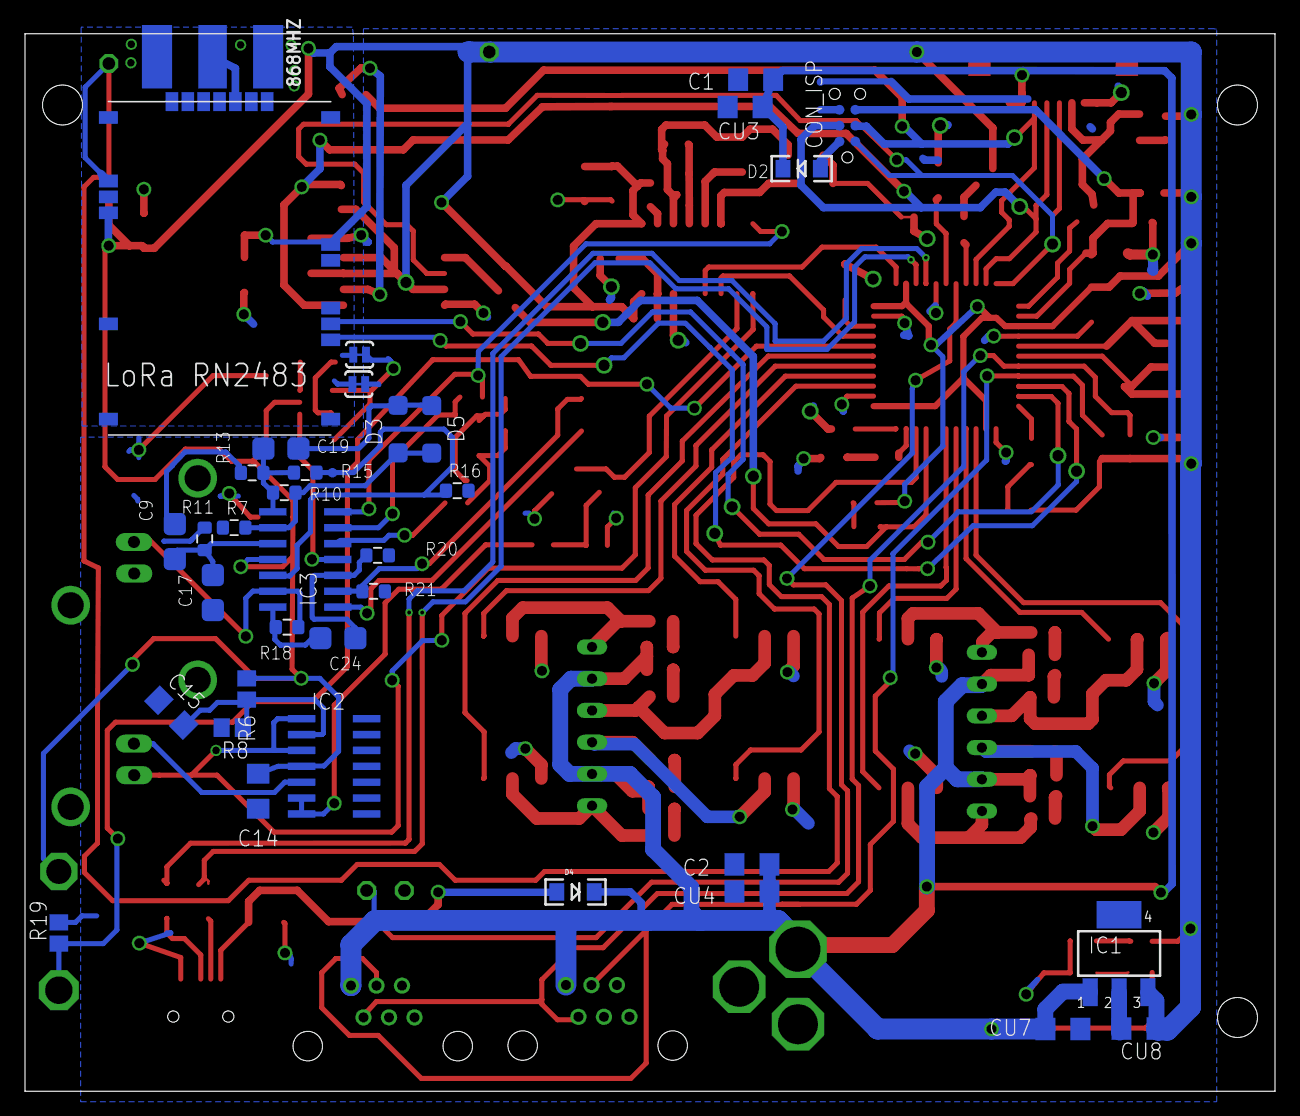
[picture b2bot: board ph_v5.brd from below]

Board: 4 copper layers, 100.0 x 84.6 mm, 142 parts (37 on the bottom side), 98 nets.

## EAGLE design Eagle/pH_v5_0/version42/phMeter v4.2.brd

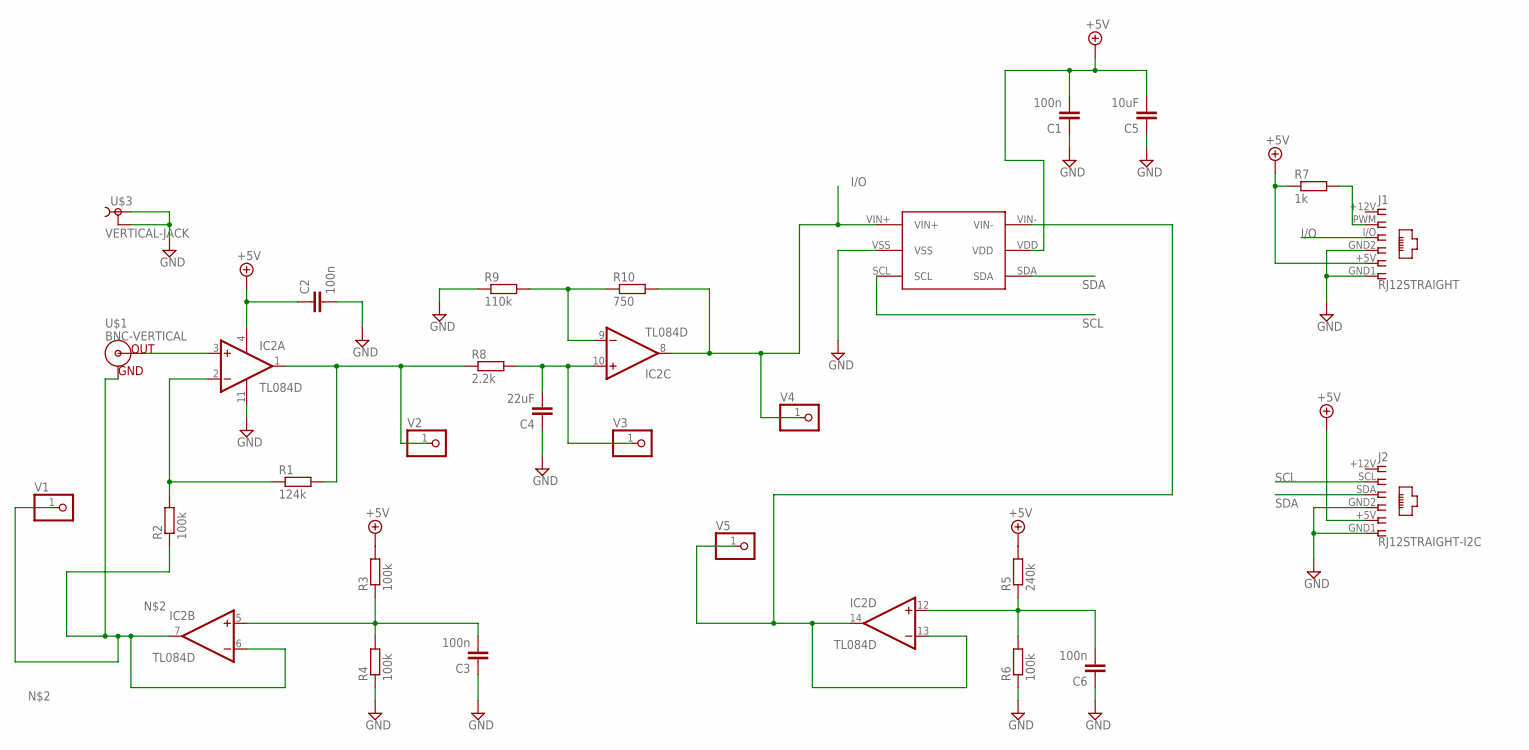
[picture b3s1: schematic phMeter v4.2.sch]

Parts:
C1, C2, C3, C6: 100n; C1206
C4: 22uF; C1206
C5: 10uF; C1206
IC2: TL084D; SO14
J1: RJ12STRAIGHT; RJ12-STRAIGHT
J2: RJ12STRAIGHT-I2C; RJ12-STRAIGHT-I2C
R1: 124k; R1206
R2, R3, R4, R6: 100k; R1206
R5: 240k; R1206
R7: 1k; R1206
R8: 2.2k; R1206
R9: 110k; R1206
R10: 750; R1206
U$1: BNC-VERTICAL
U$3: VERTICAL-JACK
U$5: MCP3425; SOT-23-6
V1, V2, V3, V4, V5: PINHD-1X1; 1X01

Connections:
+5V: C1.2, C2.1, C5.2, IC2.4 (V+), J1.+5V (5), J2.+5V (5), R3.2, R5.2, R7.1, U$5.VDD
GND: C1.1, C2.2, C3.1, C4.1, C5.1, C6.1, IC2.11 (V-), J1.GND1 (6), J1.GND2 (4), J2.GND1 (6), J2.GND2 (4), R4.1, R6.1, R9.1, U$3.P$1 (1), U$3.P$2 (2), U$5.VSS
I/O: IC2.8 (OUT), J1.I/O (3), R10.2, U$5.VIN+, V4.1
unnamed: IC2.2 (-IN), R1.1, R2.2
unnamed: IC2.6 (-IN), IC2.7 (OUT), R2.1, U$1.G (GND), V1.1
unnamed: J1.PWM (2), R7.2
unnamed: IC2.13 (-IN), IC2.14 (OUT), U$5.VIN-, V5.1
unnamed: IC2.3 (+IN), U$1.S (OUT)
unnamed: IC2.1 (OUT), R1.2, R8.1, V2.1
unnamed: C3.2, IC2.5 (+IN), R3.1, R4.2
unnamed: C4.2, IC2.10 (+IN), R8.2, V3.1
unnamed: IC2.9 (-IN), R9.2, R10.1
unnamed: C6.2, IC2.12 (+IN), R5.1, R6.2
SCL: J2.SCL (2), U$5.SCL
SDA: J2.SDA (3), U$5.SDA

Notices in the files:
parts and their libraries:
lpatiny: ©2009 ROFA.cz - modified and updated by Robert Darlington ‹rdarlington@gmail.com›
SparkFun-Connectors: Licensing: CC v3.0 Share-Alike You are welcome to use this library for commercial purposes.
